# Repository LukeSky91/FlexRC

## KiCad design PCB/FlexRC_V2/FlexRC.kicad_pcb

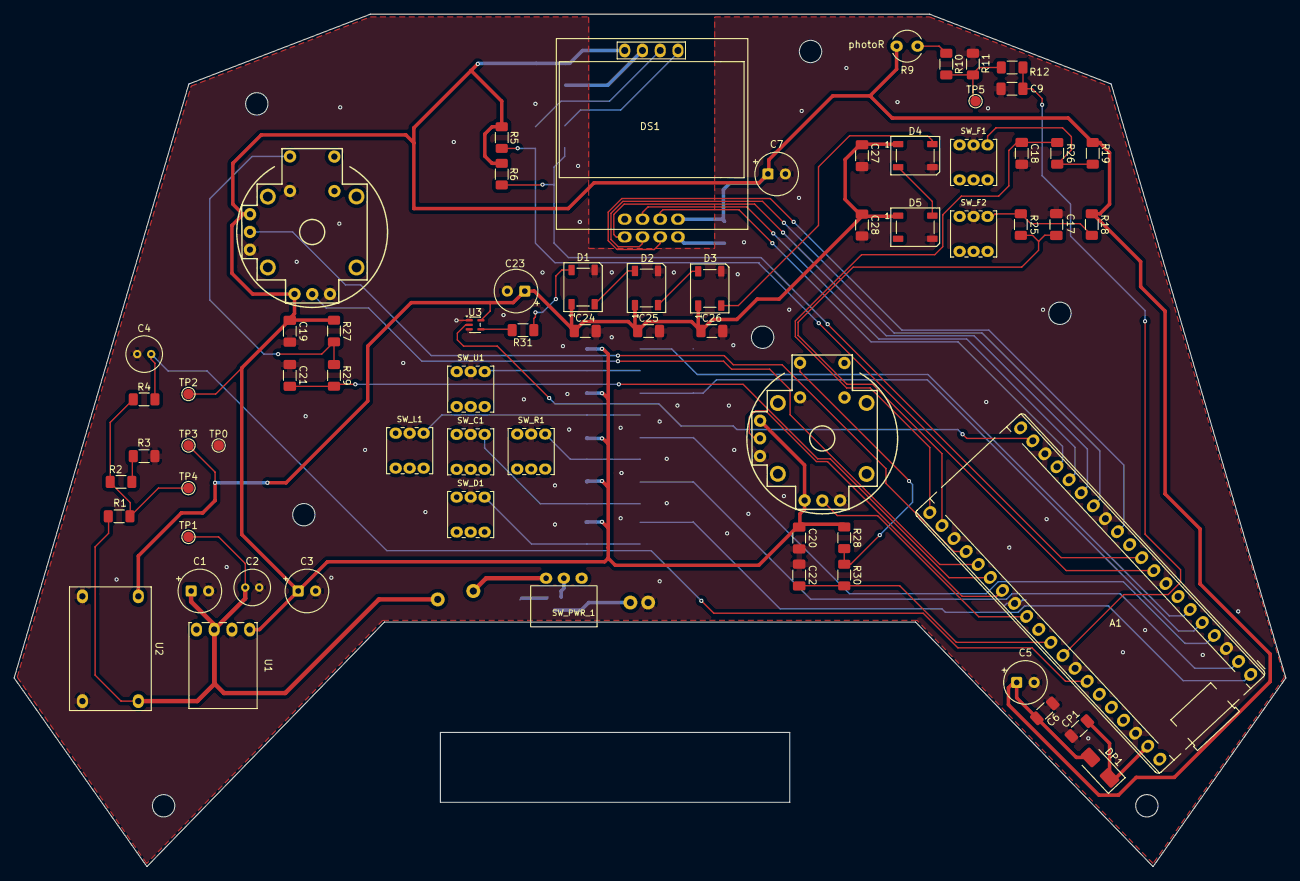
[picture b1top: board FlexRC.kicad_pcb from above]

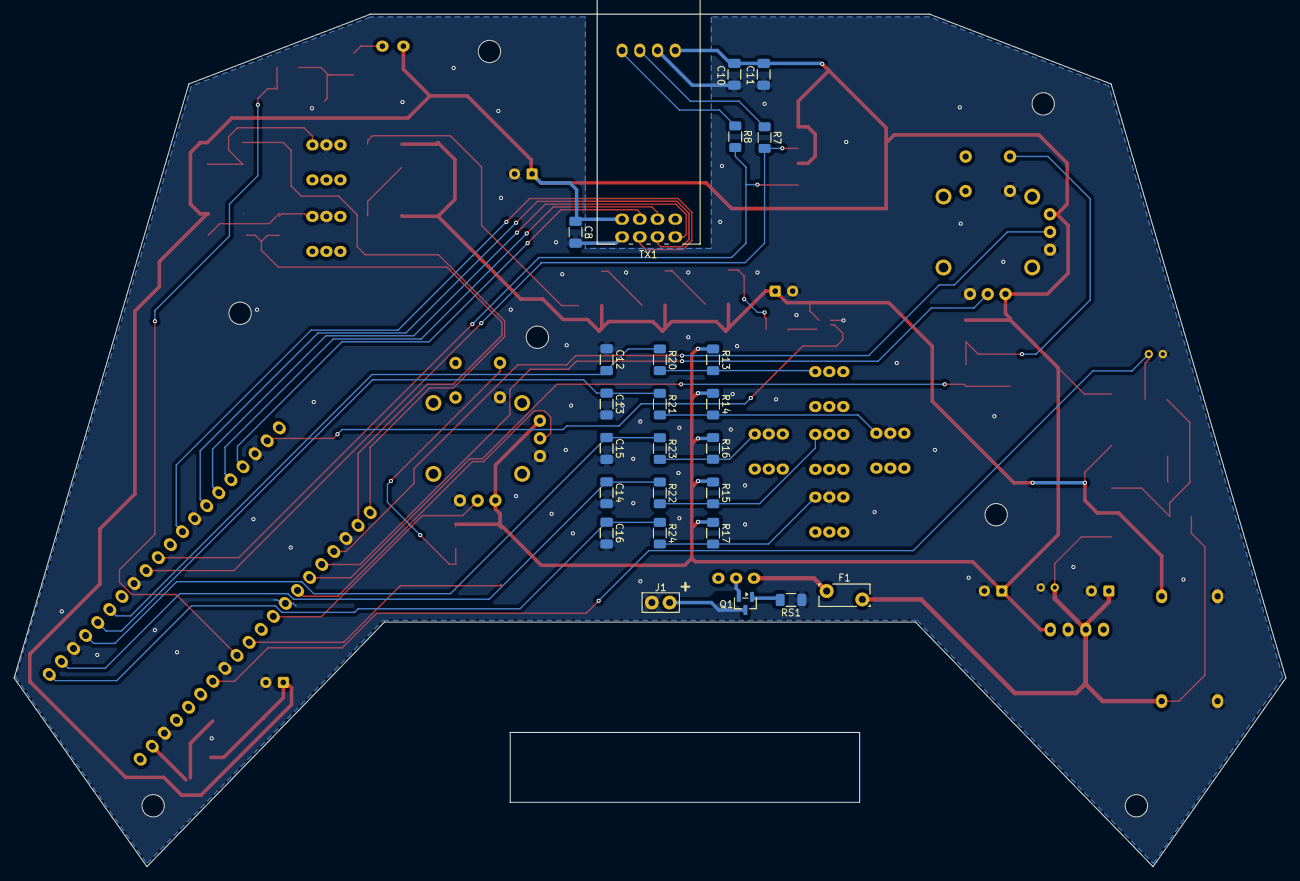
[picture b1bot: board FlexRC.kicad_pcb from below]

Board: 2 copper layers, 182.0 x 122.0 mm, 92 parts (25 on the bottom side), 53 nets.

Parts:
A1: Waveshare_23803_ESP32-S3-Pico
C1, C5, C7: 100u; CP_Radial_Tantal_D6.0mm_P2.50mm
C2, C4: 100n; C_Radial_D5.0mm_H5.0mm_P2.00mm
C3, C23: 220u; CP_Radial_Tantal_D6.0mm_P2.50mm
C6, C8, C9, C11, C12, C13, C14, C15, C16, C17, C18, C19, C20, C21, C22, C24, C25, C26, C27, C28: 100n; C_1206_3216Metric_Pad1.33x1.80mm_HandSolder
C10: 10n; C_1206_3216Metric_Pad1.33x1.80mm_HandSolder
CP1: 22u; C_1206_3216Metric_Pad1.33x1.80mm_HandSolder
D1, D2, D3, D4, D5: WS2812B; LED_WS2812B_PLCC4_5.0x5.0mm_P3.2mm
DP1: B140-E3; D_SMA
DS1: SSD1306_128x64; OLED_SSD1306_128x64_Module
F1: Polyfuse; Fuse_Bourns_MF-RG300
J1: Conn_01x02; 2pin_header_new
JOY_L_1: joystick-hall-effect; PS4_joystick
JOY_R_1: joystick-hall-effect; PS4_joystick
Q1: Q_PMOS_GSD; SOT-23
R1: 51k; R_1206_3216Metric_Pad1.30x1.75mm_HandSolder
R2, R3, R11, R13, R14, R15, R16, R17, R18, R19, R27, R28: 10k; R_1206_3216Metric_Pad1.30x1.75mm_HandSolder
R4, R12, R20, R21, R22, R23, R24, R25, R26, R29, R30: 1k; R_1206_3216Metric_Pad1.30x1.75mm_HandSolder
R5, R6: 5k1; R_1206_3216Metric_Pad1.30x1.75mm_HandSolder
R7, R8: 33R; R_1206_3216Metric_Pad1.30x1.75mm_HandSolder
R9: photoR; photoResistor
R10: 3k3; R_1206_3216Metric_Pad1.30x1.75mm_HandSolder
R31: 330R; R_1206_3216Metric_Pad1.30x1.75mm_HandSolder
RS1: 100k; R_1206_3216Metric_Pad1.30x1.75mm_HandSolder
SW_C1: PB07C; SW_PB07C_THT_6P
SW_D1: PB07C; SW_PB07C_THT_6P
SW_F1, SW_F2: PB07C; SW_PB07C_THT_6P
SW_L1: PB07C; SW_PB07C_THT_6P
SW_PWR_1: SW_SPDT; power_switch
SW_R1: PB07C; SW_PB07C_THT_6P
SW_U1: PB07C; SW_PB07C_THT_6P
TP0: GND; TestPoint_Pad_D1.5mm
TP1: 8V; TestPoint_Pad_D1.5mm
TP2: 3V3; TestPoint_Pad_D1.5mm
TP3: 5V; TestPoint_Pad_D1.5mm
TP4: Batt_Mid; TestPoint_Pad_D1.5mm
TP5: Photo_Mid; TestPoint_Pad_D1.5mm
TX1: NRF24L01_Breakout; nRF24L01_Breakout
U1: SparkFun 3.3V; AP63203 step-down BabyBuck - 3,3V 2A - SparkFun COM-18357
U2: 5V_mini_buck
U3: 74AHCT1G125; SOT-353_SC-70-5

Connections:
+3.3V: C3.1, C5.1, C6.1, C7.1, C8.1, C10.1, C11.1, C19.2, C20.2, DP1.2 (A), DS1.1 (VDD), JOY_L_1.X1 (H_3.3V), JOY_L_1.Y1 (V_3.3V), JOY_R_1.X1 (H_3.3V), JOY_R_1.Y1 (V_3.3V), R5.2, R6.2, R9.1, R13.1, R14.1, R15.1, R16.1, R17.1, R18.1, R19.1, R27.1, R28.1, TP2.1 (1_1), TX1.2 (VCC), U1.1 (OUT)
+5V: C23.1, C24.1, C25.1, C26.1, C27.1, C28.1, D1.1 (VDD), D2.1 (VDD), D3.1 (VDD), D4.1 (VDD), D5.1 (VDD), TP3.1 (1_1), U2.3 (OUT), U3.5 (VCC)
+8V: C1.1, C2.1, F1.2, R1.2, TP1.1 (1_1), U1.3 (VIN), U2.1 (VIN)
/RGBs/D1_out: D1.2 (DOUT), D2.4 (DIN)
/RGBs/D2_out: D2.2 (DOUT), D3.4 (DIN)
/RGBs/D3_out: D3.2 (DOUT), D4.4 (DIN)
/RGBs/D4_out: D4.2 (DOUT), D5.4 (DIN)
/RGBs/GP39_LS: D1.4 (DIN), R31.2
CH0: A1.24 (ADC1_CH0_GP1), JOY_L_1.Y2 (V_signal)
CH1: A1.25 (ADC1_CH1_GP2), JOY_L_1.X2 (H_signal)
CH3: A1.26 (ADC1_CH3_GP4), C21.1, R29.2
CH4: A1.27 (ADC1_CH4_GP5), JOY_R_1.Y2 (V_signal)
CH5: A1.29 (ADC1_CH5_GP6), JOY_R_1.X2 (H_signal)
CH6: A1.31 (ADC1_CH6_GP7), C22.1, R30.2
CH7: A1.32 (ADC1_CH7_GP8), C9.1, R12.2
CH8: A1.34 (ADC1_CH8_GP9), C4.1, R4.1
GND: A1.3 (GND), A1.8 (GND), A1.13 (GND), A1.18 (GND), A1.23 (GND), A1.28 (GND), A1.33 (GND), A1.38 (GND), C1.2, C2.2, C3.2, C4.2, C5.2, C6.2, C7.2, C8.2, C9.2, C10.2, C11.2, C12.2, C13.2, C14.2, C15.2, C16.2, C17.2, C18.2, C19.1, C20.1, C21.2, C22.2, C23.2, C24.2, C25.2, C26.2, C27.2, C28.2, CP1.2, D1.3 (VSS), D2.3 (VSS), D3.3 (VSS), D4.3 (VSS), D5.3 (VSS), DS1.2 (GND), J1.1, JOY_L_1.S1 (SW_COM), JOY_L_1.X3 (H_GND), JOY_L_1.Y3 (V_GND), JOY_R_1.S1 (SW_COM), JOY_R_1.X3 (H_GND), JOY_R_1.Y3 (V_GND), R3.1, R11.2, RS1.1, SW_C1.2 (B), SW_D1.2 (B), SW_F1.2 (B), SW_F2.2 (B), SW_L1.2 (B), SW_R1.2 (B), SW_U1.2 (B), TP0.1 (1_1), TX1.1 (GND), U1.2 (GND), U2.2 (GND), U2.4 (GND), U3.1, U3.3 (GND)
GP11: A1.1 (GP11), C16.1, R24.2
GP12: A1.2 (GP12), C14.1, R22.2
GP13: A1.4 (GP13), C15.1, R23.2
GP14: A1.5 (GP14), C13.1, R21.2
GP15: A1.6 (GP15), C12.1, R20.2
GP17: A1.9 (GP17), R5.1, R7.1
GP18: A1.10 (GP18), R6.1, R8.1
GP34: A1.12 (GP34), TX1.3 (CE)
GP35: A1.14 (GP35), TX1.5 (SCK)
GP36: A1.15 (GP36), TX1.7 (MISO)
GP37: A1.16 (GP37), TX1.6 (MOSI)
GP38: A1.17 (GP38), TX1.4 (~CSN)
GP39: A1.19 (GP39), U3.2
GP41: A1.22 (GP41), C17.1, R25.2
GP42: A1.21 (GP42), C18.1, R26.2
unnamed: A1.39 (VSYS), CP1.1, DP1.1 (K)
unnamed: DS1.3 (SCL), R7.2
unnamed: DS1.4 (SDA), R8.2
unnamed: J1.2, Q1.3 (D)
unnamed: JOY_L_1.S2 (SW_NO), R27.2, R29.1
unnamed: JOY_R_1.S2 (SW_NO), R28.2, R30.1
unnamed: Q1.1 (G), RS1.2
unnamed: Q1.2 (S), SW_PWR_1.2 (B)
unnamed: R1.1, R2.2, R4.2, TP4.1 (1_1)
unnamed: R2.1, R3.2
unnamed: R9.2, R10.1
unnamed: R10.2, R11.1, R12.1, TP5.1 (1_1)
unnamed: R13.2, R20.1, SW_U1.3 (C)
unnamed: R14.2, R21.1, SW_L1.3 (C)
unnamed: R15.2, R22.1, SW_C1.3 (C)
unnamed: R16.2, R23.1, SW_R1.3 (C)
unnamed: R17.2, R24.1, SW_D1.3 (C)
unnamed: R18.2, R25.1, SW_F2.3 (C)
unnamed: R19.2, R26.1, SW_F1.3 (C)
unnamed: R31.1, U3.4
unnamed: F1.1, SW_PWR_1.3 (C)

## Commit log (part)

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2026-01-11 Initial commit – FlexRC_v1
2026-01-16 0116
2026-03-14 pico_v1
2026-03-15 FlexRC_esp32_v2
2026-03-16 FlexRC_esp32_v3
2026-03-17 FlexRC_esp32_v4
2026-03-25 esp32_v5
